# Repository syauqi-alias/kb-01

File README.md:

# Komputer Basikal, KB-01

**KB-01** is a high-performance, open-source bike computer built around the Raspberry Pi Compute Module 5. Designed to function like a rugged PDA for cycling, it features NVMe storage, precise GNSS tracking, a full sensor cluster for ML-based dead reckoning, and a robust power management system with 4.5–7 hours of estimated runtime.

## 📋 Specifications

| Feature | Component / Detail |
| :--- | :--- |
| **Core** | Raspberry Pi CM5 (4GB RAM, quad Cortex-A76) |
| **Storage** | 250GB NVMe M.2 2230 (PCIe) |
| **Display** | Waveshare 3.5" LCD (MIPI DSI) |
| **GNSS** | ST Teseo-LIV4F with Taoglas FXP611.07.0092C (Passive Antenna) |
| **IMU** | Bosch BMI270 (Accel/Gyro, SPI) |
| **Magnetometer** | ST LIS2MDL (I2C) |
| **Barometer** | Bosch BMP390 (I2C) |
| **Temp/Humidity** | Sensirion SHT40 (I2C) |
| **Wheel Speed** | TI DRV5023FA (Continuous unipolar Hall switch, 30kHz BW) |
| **Battery** | 10,000mAh Li-ion 1160100 (3.7V / 37Wh) |
| **Charger** | TI BQ25895 (I2C-configurable, USB BC1.2 detection) |
| **Fuel Gauge** | Maxim MAX17048 (I2C) |
| **Boost Converter** | TI TPS61022 (5V output, 8A valley current limit) |
| **USB Mux** | TI TS3USB30E (2:1 USB 2.0, auto-switching via BQ25895 DSEL) |
| **User Input** | Rotary encoder (A/B + push) + 2 buttons |
| **Audio** | Passive electromagnetic buzzer (PWM-driven via 2N7002 N-FET) |
| **Connectivity** | USB 2.0 (device/peripheral mode for GPX file transfer + charging) |

## ⚡ Power System

The power architecture handles high current loads from the CM5 and NVMe while ensuring safe battery management.

```
USB-C → BQ25895 (VBUS) → SYS → TPS61022 (VIN) → 5V → CM5
                ↕
            Battery
```

* **Charger / Power Path:** [TI BQ25895](https://www.ti.com/product/BQ25895)
    * Charges the battery while simultaneously powering the system via SYS rail.
    * Integrated USB BC1.2 detection for automatic source identification (SDP/CDP/DCP).
    * Input Current Optimizer (ICO) negotiates maximum power from USB source.
    * Ship mode via BATFET for zero-quiescent shutdown.
* **Fuel Gauge:** [Maxim MAX17048](https://www.analog.com/en/products/max17048.html)
    * ModelGauge algorithm — no sense resistor required.
    * Provides accurate SoC% and voltage reporting over I2C.
* **Boost Converter:** [TI TPS61022](https://www.ti.com/product/TPS61022)
    * Provides a fixed 5V output from 3.0–4.5V battery input.
    * EN tied to VIN (always on when SYS is live); MODE tied to GND (PFM for light-load efficiency).
    * Feedback resistors: R1 = 732kΩ, R2 = 100kΩ (per TI reference design).
* **USB-C:**
    * CC1/CC2: 5.1kΩ pull-downs to GND (sink device).
    * D+/D−: Routed via TS3USB30E multiplexer — Channel 1 to BQ25895 (BC1.2 detection), Channel 2 to CM5 USB (data transfer).
    * Mux control: BQ25895 DSEL pin drives TS3USB30E SEL (automatic, no GPIO needed).
    * CM5 USB configured as device/peripheral via `dtoverlay=dwc2,dr_mode=peripheral`.
* **Battery Life:** ~4.5 hours (max load) to ~7 hours (typical load).

## 🔌 Bus Architecture

| Bus | GPIOs | Devices | Notes |
| :--- | :--- | :--- | :--- |
| **I2C1** | GPIO2/3 | BQ25895, MAX17048 | 1.8kΩ built-in pull-ups (do NOT add external) |
| **I2C2** | GPIO4/5 | LIS2MDL, BMP390, SHT40 | 4.7kΩ external pull-ups required |
| **SPI0** | GPIO8–11 | BMI270 | Mode 0, max 10MHz |
| **UART0** | GPIO14/15 | Teseo-LIV4F | 9600 baud default, TX/RX crossover |
| **DSI0** | DISP0 connector | Waveshare 3.5" | Copied from CM5 IO board |
| **PCIe** | PCIe connector | NVMe SSD | Copied from CM5 IO board |

## 📡 Sensor Cluster & ML Dead Reckoning

The sensor cluster enables ML-based location prediction when GNSS is unavailable (tunnels, dense tree cover, urban canyons).

* **Inputs:** BMI270 (acceleration/rotation), LIS2MDL (heading), BMP390 (altitude), DRV5023FA (wheel speed/distance)
* **Ground truth:** Teseo-LIV4F GNSS position during training
* **Approach:** Extended Kalman filter or RNN; wheel speed removes velocity drift ambiguity
* **Wheel Speed Sensor:** DRV5023FA is a continuous-sensing unipolar Hall switch (not sampled) with 30kHz bandwidth — it never misses a pulse regardless of wheel speed. Single south-facing magnet on spoke, open-drain output with 10kΩ pull-up.

## 🔊 Audio Alerts

A passive electromagnetic buzzer (e.g. MLT-8530) driven by PWM on GPIO7 through a 2N7002 N-channel MOSFET. Used for turn-by-turn navigation alerts, speed warnings, button feedback, and low battery warnings.

```
GPIO7 → 100Ω → gate ──┬── 2N7002 drain ──── Buzzer (−)
                       │                          │
                     10kΩ                     Buzzer (+) → 3.3V
                       │                          │
                      GND              1N4148 ──|◄──┘ (flyback diode)
```

## 🖥️ Software Architecture

* **Language:** C (with pthreads for multi-core)
* **GUI:** LVGL (renders directly to framebuffer, no X11/Wayland)
* **Kernel:** PREEMPT_RT patched Linux for deterministic interrupt handling
* **Core allocation:**
    * Core 0 — UI rendering + wheel speed ISR (highest priority)
    * Core 1 — Sensor acquisition (I2C/SPI reads)
    * Core 2 — GNSS processing (UART/NMEA parsing)
    * Core 3 — ML inference + data logging

## 🛠️ Hardware Design Notes

* **Space Optimization:** The boost converter is placed underneath the M.2 NVMe drive clearance to minimize the PCB footprint.
* **Antenna:** Uses a passive flexible polymer antenna (Taoglas FXP611) for GNSS.
* **Mounting:** Designed to accommodate standard 3.5" display mounting points.
* **GPIO0:** Left as spare — HAT EEPROM pin (I2C0/ID_SD), available for future expansion.

### Layer Stackup (6-layer, 1.6 mm, AISLER)

Stackup source: [AISLER 6-layer 1.6 mm 35 µm](https://community.aisler.net/t/6-layers-1-6mm-35-m-stackup/5458). Copper is 35 µm on all layers. Impedance-controlled nets stay on the outer layers only, referenced to the adjacent solid GND plane (same approach as the Raspberry Pi CM5 IO board).

```
Layer    Role                     Reference   Dielectric below
F.Cu     Signal — low-speed       In1 GND     2 × 2116 prepreg, 230 µm, Er 4.25
In1.Cu   GND plane — never split  —           FR4 core,          300 µm, Er 4.5
In2.Cu   Signal — GPIO / SD / I2C In1 GND     3 × 2116 prepreg, 345 µm, Er 4.25
In3.Cu   Power — split pours      —           FR4 core,          300 µm, Er 4.5
In4.Cu   GND plane — never split  —           2 × 2116 prepreg, 230 µm, Er 4.25
B.Cu     Signal — high-speed      In4 GND     —
```

* **B.Cu (high-speed side):** CM5 module, M.2 NVMe, DSI connector, Teseo GNSS and SMA are all on B.Cu, so PCIe, DSI0 and the GNSS RF trace route bottom-to-bottom with no layer changes. Net classes: `DP_90_Outer` (PCIe, USB 2.0), `DP_100_Outer` (DSI0), `SE_50_Outer` (GNSS RF).
* **F.Cu:** USB-C, charger, fuel gauge, sensors, UI. USB 2.0 D+/D− (J3 → TS3USB30E → BQ25895) stays on F.Cu.
* **In2.Cu:** route predominantly one axis (along the 120 mm dimension) — it faces In3 with no plane between them.
* **In3.Cu:** pours only, no traces: `+5V`, `Vsys`, `+3V3`, `VBUS`, `+1.8v`, `3.3V_GNSS`, `M.2_3v3`.
* **Stitching:** via fence between In1 and In4 along the RF trace and around the CM5 high-speed region. Fill unused In2 area with GND to balance copper against In3.

See [ROUTING.md](ROUTING.md) for the routing order and per-net constraints.

## ⚙️ config.txt

```ini
dtparam=i2c_arm=on
dtoverlay=i2c2-pi5,pins_4_5
dtparam=spi=on
enable_uart=1
dtoverlay=dwc2,dr_mode=peripheral
```

## ⚠️ Disclaimer

This project is currently in the **prototype/brainstorming phase**.

* Battery life estimates (4.5–7 hours) are theoretical and based on datasheet typical values.
* USB-PD is not supported with passive CC resistors (5V input only).
* The CM5 + NVMe combination draws significant power — consider NVMe power states for optimisation.

## 🔗 References & Credits

* Designed by [Syauqi Alias](https://syauqi-alias.github.io/)
* Read the full project log here: [Projects Brainstorming](https://syauqi-alias.github.io/jekyll/2023-06-10-idea.html#komputer-basikal-kb-01-bike-computer)

## 📄 License

[MIT License](LICENSE)

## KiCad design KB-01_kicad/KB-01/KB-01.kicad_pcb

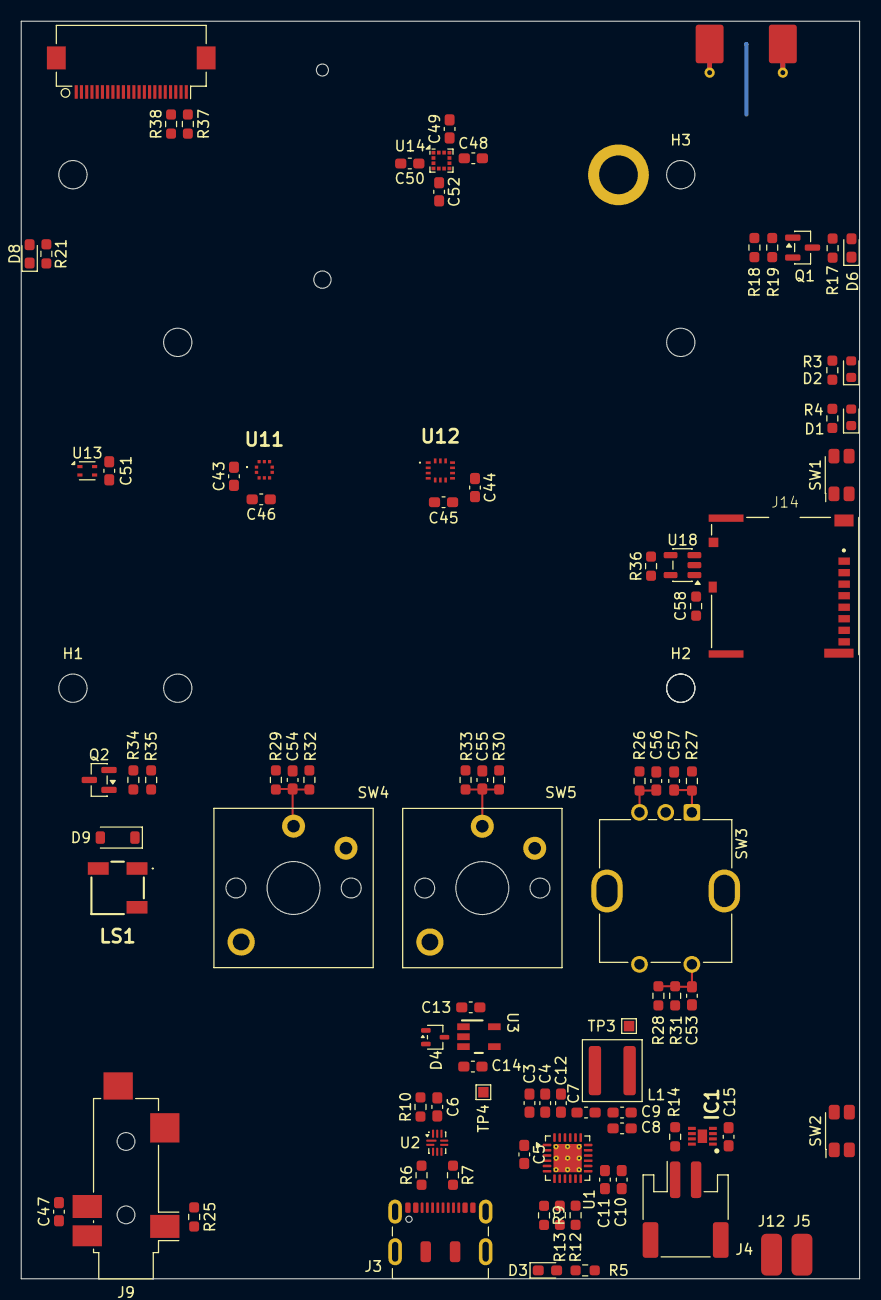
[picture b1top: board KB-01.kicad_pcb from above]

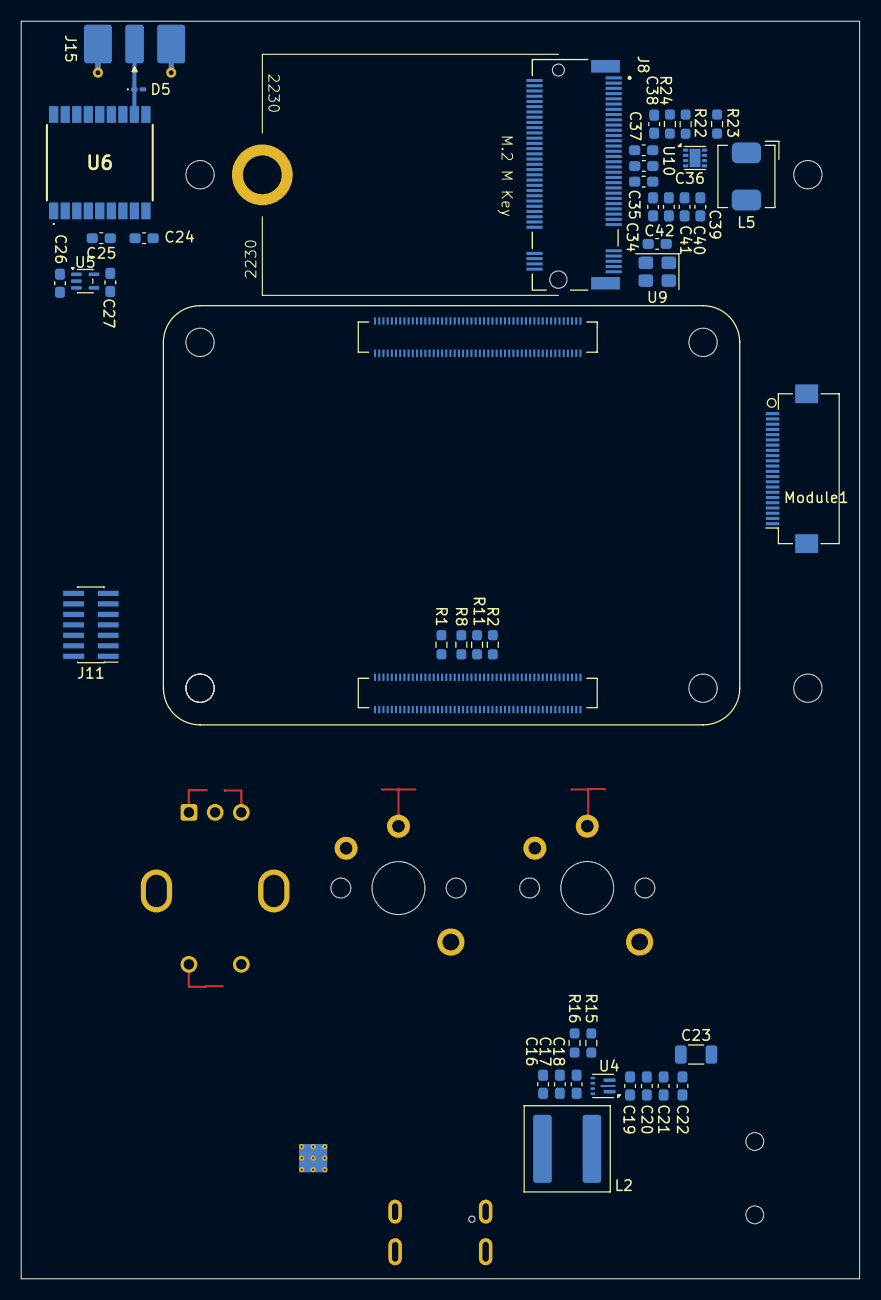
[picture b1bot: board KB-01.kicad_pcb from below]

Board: 6 copper layers, 80.0 x 120.0 mm, 138 parts (43 on the bottom side), 127 nets.

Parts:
C3, C8, C9, C10: 10uF 25V; C_0603_1608Metric_Pad1.08x0.95mm_HandSolder
C4, C11, C15: 0.1uF 25V; C_0603_1608Metric_Pad1.08x0.95mm_HandSolder
C5, C13: 1uF 25V; C_0603_1608Metric_Pad1.08x0.95mm_HandSolder
C6, C34, C37, C47: 0.1uF 10V; C_0603_1608Metric_Pad1.08x0.95mm_HandSolder
C7: 47nF 25V; C_0603_1608Metric_Pad1.08x0.95mm_HandSolder
C12, C14: 4.7uF 16V; C_0603_1608Metric_Pad1.08x0.95mm_HandSolder
C16, C17, C19, C20, C21, C22: 22uF 16V; C_0603_1608Metric_Pad1.08x0.95mm_HandSolder
C18: 0.1uF 16V; C_0603_1608Metric_Pad1.08x0.95mm_HandSolder
C23: 47uF 16V; R_1206_3216Metric
C24, C43, C44, C45, C46, C48, C50, C51, C53, C54, C55, C56, C57: 100nF 6.3V; C_0603_1608Metric_Pad1.08x0.95mm_HandSolder
C25, C49: 10uF 6.3V; C_0603_1608Metric_Pad1.08x0.95mm_HandSolder
C26, C27: 1uF 16V; C_0603_1608Metric_Pad1.08x0.95mm_HandSolder
C35, C36, C39, C40, C41, C42: 10uF10V; C_0603_1608Metric_Pad1.08x0.95mm_HandSolder
C38: 4.7nF 10V; C_0603_1608Metric_Pad1.08x0.95mm_HandSolder
C52: 220nF 25V; C_0603_1608Metric_Pad1.08x0.95mm_HandSolder
C58: 10uF 6.3V; R_0603_1608Metric_Pad0.98x0.95mm_HandSolder
D1: LED Green; LED_0603_1608Metric
D2: LED Red; LED_0603_1608Metric
D3, D8: Green; D_0603_1608Metric_Pad1.05x0.95mm_HandSolder
D4: BAT54-05W; SOT-323_SC-70
D5: SM15T36CA; D_0201_0603Metric_Pad0.64x0.40mm_HandSolder
D6: LED Red; LED_0603_1608Metric_Pad1.05x0.95mm_HandSolder
D9: 1N4148W; D_SOD-123
H1, H2, H3, H4: MountingHole; MountingHole_2.7mm_M2.5_DIN965
IC1: MAX17048G+T10; SON50P200X200X80-9N-D
J1, J13: Conn_01x22_MountingPin; Hirose_FH12-22S-0.5SH_1x22-1MP_P0.50mm_Horizontal
J3: USB_C_Receptacle_USB2.0_14P; USB_C_Receptacle_JAE_DX07S016JA1R1500
J4: Conn_01x02_MountingPin; JST_PH_S2B-PH-SM4-TB_1x02-1MP_P2.00mm_Horizontal
J5, J12: Conn_01x01_Socket; SolderWirePad_1x01_SMD_2x4mm
J8: Bus_M.2_Socket_M; M.2 M Key socket
J9: AudioJack3_SwitchTR; Jack_3.5mm_CUI_SJ2-3593D-SMT_Horizontal
J11: Conn_02x07_Odd_Even; PinHeader_2x07_P1.00mm_Vertical_SMD
J14: Micro_SD_Card_Det; SDCARD_MOLEX_503398-1892
J15: Conn_Coaxial; SMA_Molex_73251-2120_EdgeMount_Horizontal
L1: 1.0uH; L_Coilcraft_XAL5030-XXX
L2: 1uH 21.8A; L_Coilcraft_XAL7030-102
L5: 2.2uH; L_Bourns_SRP5030CC
LS1: CMT-0502-03-SMT-TR; CMT050203SMTTR
Module1: ComputeModule5-CM5; Raspberry-Pi-5-Compute-Module
Q1: MMBT3904; SOT-23
Q2: 2N7002; SOT-23
R1, R2, R18: 4.7k; R_0603_1608Metric_Pad0.98x0.95mm_HandSolder
R3, R4, R21, R31, R32, R33: 1k; R_0603_1608Metric_Pad0.98x0.95mm_HandSolder
R5: 2.21K; R_0603_1608Metric_Pad0.98x0.95mm_HandSolder
R6, R7: 5.1k; R_0603_1608Metric_Pad0.98x0.95mm_HandSolder
R8, R10, R11, R12, R13, R14, R19, R25, R26, R27, R28, R29, R30, R35: 10k; R_0603_1608Metric_Pad0.98x0.95mm_HandSolder
R9: 133; R_0603_1608Metric_Pad0.98x0.95mm_HandSolder
R15: 750k; R_0603_1608Metric_Pad0.98x0.95mm_HandSolder
R16: 100k; R_0603_1608Metric_Pad0.98x0.95mm_HandSolder
R17: 330; R_0603_1608Metric_Pad0.98x0.95mm_HandSolder
R22, R36: 10K 1%; R_0603_1608Metric_Pad0.98x0.95mm_HandSolder
R23: 100k 1%; R_0603_1608Metric_Pad0.98x0.95mm_HandSolder
R24, R37, R38: 2.2K 1%; R_0603_1608Metric_Pad0.98x0.95mm_HandSolder
R34: 180; R_0603_1608Metric_Pad0.98x0.95mm_HandSolder
SW1: Right angle Tact button; SW_SPST_EVQP7A
SW2: Power button; SW_SPST_EVQP7A
SW3: RotaryEncoder_Switch_MP; RotaryEncoder_Bourns_Vertical_PEC12R-3x17F-Sxxxx
SW4, SW5: SW_Push; SW_Kailh_Choc_V1V2_1.00u
TP3, TP4: TestPoint; TestPoint_Pad_1.0x1.0mm
U1: BQ25895; Texas_RTW_WQFN-24-1EP_4x4mm_P0.5mm_EP2.7x2.7mm_ThermalVias
U2: TS3USB30ERSWR; UQFN-10_1.4x1.8mm_P0.4mm
U3: TLV70430DBVR; DBV0005A_M
U4: TPS61022; Texas_RWU0007A_VQFN-7_2x2mm_P0.5mm
U5: TLV773_SOT353; SOT-353_SC-70-5
U6: TESEO-LIV4F; TESEOLIV4FTR
U9: ASEK-32.768KHZ-L-R-T; Crystal_SMD_3225-4Pin_3.2x2.5mm
U10: AP3441SHE-7B; DFN-8-1EP_2x2mm_P0.5mm_EP1.05x1.75mm
U11: BMP581
U12: BMI270
U13: SHT40; Sensirion_DFN-4_1.5x1.5mm_P0.8mm_SHT4x_NoCentralPad
U14: LIS2MDL; LGA-12_2x2mm_P0.5mm
U18: RT9742GGJ5 / NCP380HSN10AAT1G; SOT-23-5

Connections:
+3V3: C43.2, C44.1, C45.1, C46.1, C47.1, C48.1, C49.1, C50.1, C51.1, D1.2 (A), D2.2 (A), D9.1 (K), J1.22, J9.R, J9.RN, J13.22, LS1.1 (+), Module1.78 (GPIO_VREF(1.8v/3.3v_Input)), Module1.84 (+3.3v_(Output)), Module1.86 (+3.3v_(Output)), R1.1, R2.1, R25.1, R26.1, R27.1, R28.1, R29.1, R30.1, R36.1, R37.1, R38.1, U11.1 (VDDIO), U11.5 (SDO), U11.6 (CSB), U11.10 (VDD), U12.5 (VDDIO), U12.8 (VDD), U13.3 (VDD), U14.3 (~CS), U14.9 (Vdd), U14.10 (Vdd_IO), U18.5 (IN)
+3V_CHRG: C6.1, C14.1, Module1.76 (VBAT), R8.1, R10.2, R14.1, TP4.1 (1_1), U2.9 (VCC), U3.3 (OUT)
+5V: C19.1, C20.1, C21.1, C22.1, C23.1, C26.1, C35.1, C36.1, C37.1, Module1.77 (+5v_(Input)), Module1.79 (+5v_(Input)), Module1.81 (+5v_(Input)), Module1.83 (+5v_(Input)), Module1.85 (+5v_(Input)), Module1.87 (+5v_(Input)), R15.1, U4.3 (VOUT), U5.1 (IN), U10.3 (VIN)
/Battery_charger/CHG_D+: U1.2 (D+), U2.1 (D1+)
/Battery_charger/CHG_D-: U1.3 (D-), U2.7 (D1-)
/Battery_charger/Fuel_G: C10.1, C11.1, C15.1, D4.2 (A), IC1.2 (CELL), IC1.3 (VDD), J4.1, U1.13 (BAT), U1.14 (BAT)
/Battery_charger/MUX_D+: Module1.105 (USB2_P), U2.2 (D2+)
/Battery_charger/MUX_D-: Module1.103 (USB2_N), U2.6 (D2-)
/Battery_charger/RESET: SW2.2, U1.12 (~QON)
/Battery_charger/SEL: R10.1, U1.24 (DSEL), U2.10 (S)
/Battery_charger/USB_D+: J3.A6 (D+), J3.B6 (D+), U2.5 (D-)
/Battery_charger/USB_D-: J3.A7 (D-), J3.B7 (D-), U2.3 (D+)
/Battery_charger/Vsys: C8.1, C9.1, C16.1, C17.1, C18.1, L1.2, L2.1, R5.2, TP3.1 (1_1), U1.15 (SYS), U1.16 (SYS), U4.5 (EN), U4.7 (VIN)
/CM5_GPIO/+1.8v: Module1.88 (+1.8v_(Output)), Module1.90 (+1.8v_(Output))
/CM5_GPIO/CAM_GPIO0: J13.17, Module1.97 (CAM_GPIO0)
/CM5_GPIO/CAM_GPIO1: J9.S, Module1.100 (CAM_GPIO1), R25.2
/CM5_GPIO/EEPROM_nWP: J11.4, Module1.20 (EEPROM_nWP)
/CM5_GPIO/GPIO2: IC1.8 (SDA), Module1.58 (GPIO2), U1.6 (SDA)
/CM5_GPIO/GPIO3: IC1.7 (SCL), Module1.56 (GPIO3), U1.5 (SCL)
/CM5_GPIO/GPIO4: Module1.54 (GPIO4), R2.2, U11.4 (SDI), U13.1 (SDA), U14.4 (SDA/SDI/SDO)
/CM5_GPIO/GPIO5: Module1.34 (GPIO5), R1.2, U11.2 (SCK), U13.2 (SCL), U14.1 (SCL/SPC)
/CM5_GPIO/GPIO6: Module1.30 (GPIO6), R33.1
/CM5_GPIO/GPIO7: Module1.37 (GPIO7), R34.1
/CM5_GPIO/GPIO8: Module1.39 (GPIO8), U12.12 (CSB)
/CM5_GPIO/GPIO9: Module1.40 (GPIO9), U12.1 (SDO)
/CM5_GPIO/GPIO10: Module1.44 (GPIO10), U12.14 (SDX)
/CM5_GPIO/GPIO11: Module1.38 (GPIO11), U12.13 (SCX)
/CM5_GPIO/GPIO12: C57.1, Module1.31 (GPIO12), R27.2, SW3.A
/CM5_GPIO/GPIO13: C56.1, Module1.28 (GPIO13), R26.2, SW3.B
/CM5_GPIO/GPIO14: Module1.55 (GPIO14), U6.3 (UART-RX)
/CM5_GPIO/GPIO15: Module1.51 (GPIO15), U6.2 (UART-TX)
/CM5_GPIO/GPIO16: Module1.29 (GPIO16), U6.9 (~RESET)
/CM5_GPIO/GPIO17: Module1.50 (GPIO17), R11.1, U1.9 (~CE)
/CM5_GPIO/GPIO18: Module1.49 (GPIO18), R31.2
/CM5_GPIO/GPIO19: Module1.26 (GPIO19), R32.1
/CM5_GPIO/GPIO20: Module1.27 (GPIO20), U6.5 (WAKEUP)
/CM5_GPIO/GPIO21: Module1.25 (GPIO21), U5.3 (EN)
/CM5_GPIO/GPIO22: IC1.5 (~ALRT), Module1.46 (GPIO22), R14.2
/CM5_GPIO/GPIO23: Module1.47 (GPIO23), U12.4 (INT1)
/CM5_GPIO/GPIO24: Module1.45 (GPIO24), U14.7 (DRDY)
/CM5_GPIO/GPIO25: Module1.41 (GPIO25), U11.7 (INT)
/CM5_GPIO/GPIO26: Module1.24 (GPIO26), U12.9 (INT2)
/CM5_GPIO/GPIO27: Module1.48 (GPIO27), R8.2, U1.7 (~INT)
/CM5_GPIO/ID_SC: J13.20, Module1.35 (ID_SC), R38.2
/CM5_GPIO/ID_SD: J13.21, Module1.36 (ID_SD), R37.2
/CM5_GPIO/PMIC_ENABLE: J11.12, Module1.99 (PMIC_ENABLE)
/CM5_GPIO/PWR_BUT: J11.14, Module1.92 (PWR_BUT), SW1.1
/CM5_GPIO/SD_CLK: J14.5 (CLK), Module1.57 (SD_CLK)
/CM5_GPIO/SD_CMD: J14.3 (CMD), Module1.62 (SD_CMD)
/CM5_GPIO/SD_DAT0: J14.7 (DAT0), Module1.63 (SD_DAT0)
/CM5_GPIO/SD_DAT1: J14.8 (DAT1), Module1.67 (SD_DAT1)
/CM5_GPIO/SD_DAT2: J14.1 (DAT2), Module1.69 (SD_DAT2)
/CM5_GPIO/SD_DAT3: J14.2 (DAT3/CD), Module1.61 (SD_DAT3)
/CM5_GPIO/SD_PWR: C58.1, J14.4 (VDD), U18.1 (OUT)
/CM5_GPIO/SD_PWR_ON: Module1.75 (SD_PWR_ON), R36.2, U18.4 (EN)
/CM5_GPIO/SYNC_OUT: J11.6, Module1.18 (Ethernet_SYNC_OUT(3.3v))
/CM5_GPIO/USBOTG: J11.10, Module1.101 (USB_OTG_ID)
/CM5_GPIO/nPWR_LED: Module1.95 (LED_nPWR), R3.2
/CM5_GPIO/nRPIBOOT: J11.2, Module1.93 (nRPIBOOT)
/CM5_high_speed/DPHY0_C_N: J1.8, Module1.127 (MIPI0_C_N)
/CM5_high_speed/DPHY0_C_P: J1.9, Module1.129 (MIPI0_C_P)
/CM5_high_speed/DPHY0_D0_N: J1.2, Module1.115 (MIPI0_D0_N)
/CM5_high_speed/DPHY0_D0_P: J1.3, Module1.117 (MIPI0_D0_P)
/CM5_high_speed/DPHY0_D1_N: J1.5, Module1.121 (MIPI0_D1_N)
/CM5_high_speed/DPHY0_D1_P: J1.6, Module1.123 (MIPI0_D1_P)
/CM5_high_speed/DPHY0_D2_N: J1.11, Module1.133 (MIPI0_D2_N)
/CM5_high_speed/DPHY0_D2_P: J1.12, Module1.135 (MIPI0_D2_P)
/CM5_high_speed/DPHY0_D3_N: J1.14, Module1.139 (MIPI0_D3_N)
/CM5_high_speed/DPHY0_D3_P: J1.15, Module1.141 (MIPI0_D3_P)
/CM5_high_speed/DPHY1_C_N: J13.8, Module1.187 (MIPI1_C_N)
/CM5_high_speed/DPHY1_C_P: J13.9, Module1.189 (MIPI1_C_P)
/CM5_high_speed/DPHY1_D0_N: J13.2, Module1.175 (MIPI1_D0_N)
/CM5_high_speed/DPHY1_D0_P: J13.3, Module1.177 (MIPI1_D0_P)
/CM5_high_speed/DPHY1_D1_N: J13.5, Module1.181 (MIPI1_D1_N)
/CM5_high_speed/DPHY1_D1_P: J13.6, Module1.183 (MIPI1_D1_P)
/CM5_high_speed/DPHY1_D2_N: J13.11, Module1.193 (MIPI1_D2_N)
/CM5_high_speed/DPHY1_D2_P: J13.12, Module1.195 (MIPI1_D2_P)
/CM5_high_speed/DPHY1_D3_N: J13.14, Module1.194 (MIPI1_D3_N)
/CM5_high_speed/DPHY1_D3_P: J13.15, Module1.196 (MIPI1_D3_P)
/CM5_high_speed/PCIE_CLK_N: J8.53 (REFCLKn), Module1.112 (PCIe_CLK_N)
/CM5_high_speed/PCIE_CLK_P: J8.55 (REFCLKp), Module1.110 (PCIe_CLK_P)
/CM5_high_speed/PCIE_PWR_EN: Module1.106 (PCIE_PWR_EN), R23.1, U10.7 (EN)
/CM5_high_speed/PCIE_RX_N: J8.43 (PETp0), Module1.118 (PCIe_RX_N)
/CM5_high_speed/PCIE_RX_P: J8.41 (PETn0), Module1.116 (PCIe_RX_P)
/CM5_high_speed/PCIE_TX_N: J8.49 (PERp0), Module1.124 (PCIe_TX_N)
/CM5_high_speed/PCIE_TX_P: J8.47 (PERn0), Module1.122 (PCIe_TX_P)
/CM5_high_speed/PCIE_nCLKREQ: J8.52 (~CLKREQ), Module1.102 (PCIe_nCLKREQ)
/CM5_high_speed/PCIE_nRST: J8.50 (~PERST), Module1.109 (PCIe_nRST)
/CM5_high_speed/PCIE_nWAKE: J8.54 (~PEWAKE), Module1.104 (PCIE_nWAKE)
/CM5_high_speed/SCL0: J1.20, Module1.80 (SCL0)
/CM5_high_speed/SDA0: J1.21, Module1.82 (SDA0)
/GNSS/3.3V_GNSS: C24.1, C25.1, C27.1, R17.1, U5.5 (OUT), U6.6 (VBAT), U6.8 (VCC)
/GNSS/GNSS_PPS: R18.1, U6.4 (PPS)
/PCIe_NVMe/FB: C38.2, R22.2, R24.1, U10.1 (FB)
/PCIe_NVMe/M.2_3v3: C34.1, C38.1, C39.1, C40.1, C41.1, C42.1, D8.2 (A), J8.2 (3.3V), J8.4 (3.3V), J8.12 (3.3V), J8.14 (3.3V), J8.16 (3.3V), J8.18 (3.3V), J8.70 (3.3V), J8.72 (3.3V), J8.74 (3.3V), L5.2, R22.1, U9.1 (EN), U9.4 (VDD)
GND: C3.2, C4.2, C5.2, C6.2, C8.2, C9.2, C10.2, C11.2, C12.2, C13.2, C14.2, C15.2, C16.2, C17.2, C18.2, C19.2, C20.2, C21.2, C22.2, C23.2, C24.2, C25.2, C26.2, C27.2, C34.2, C35.2, C36.2, C37.2, C39.2, C40.2, C41.2, C42.2, C43.1, C44.2, C45.2, C46.2, C47.2, C48.2, C49.2, C50.2, C51.2, C52.2, C53.2, C54.2, C55.2, C56.2, C57.2, C58.2, D5.2 (A2), IC1.1 (CTG), IC1.4 (GND), IC1.6 (QSTRT), IC1.9 (EP), J1.1, J1.4, J1.7, J1.10, J1.13, J1.16, J1.19, J1.MP (MountPin), J3.A1 (GND), J3.A12 (GND), J3.B1 (GND), J3.B12 (GND), J3.S1 (SHIELD), J4.2, J4.MP (MountPin), J8.1 (GND), J8.3 (GND), J8.9 (GND), J8.15 (GND), J8.21 (GND), J8.27 (GND), J8.33 (GND), J8.39 (GND), J8.45 (GND), J8.51 (GND), J8.57 (GND), J8.71 (GND), J8.73 (GND), J8.75 (GND), J8.M1 (GND2230), J8.S1, J8.S2, J9.T, J9.TN, J11.1, J11.3, J11.5, J11.7, J11.9, J11.11, J11.13, J12.1 (Pin_1_1), J13.1, J13.4, J13.7, J13.10, J13.13, J13.16, J13.19, J13.MP (MountPin), J14.6 (VSS), J14.11 (SHIELD), J15.2 (Ext), Module1.1 (GND), Module1.2 (GND), Module1.7 (GND), Module1.8 (GND), Module1.13 (GND), Module1.14 (GND), Module1.22 (GND), Module1.23 (GND), Module1.32 (GND), Module1.33 (GND), Module1.42 (GND), Module1.43 (GND), Module1.52 (GND), Module1.53 (GND), Module1.59 (GND), Module1.60 (GND), Module1.65 (GND), Module1.66 (GND), Module1.71 (GND), Module1.74 (GND), Module1.98 (GND), Module1.107 (GND), Module1.108 (GND), Module1.113 (GND), Module1.114 (GND), Module1.119 (GND), Module1.120 (GND), Module1.125 (GND), Module1.126 (GND), Module1.131 (GND), Module1.132 (GND), Module1.137 (GND), Module1.138 (GND), Module1.144 (GND), Module1.150 (GND), Module1.155 (GND), Module1.156 (GND), Module1.161 (GND), Module1.162 (GND), Module1.167 (GND), Module1.168 (GND), Module1.173 (GND), Module1.174 (GND), Module1.179 (GND), Module1.180 (GND), Module1.185 (GND), Module1.186 (GND), Module1.191 (GND), Module1.192 (GND), Module1.197 (GND), Module1.198 (GND), Q1.2 (E), Q2.2 (S), R6.2, R7.1, R9.2, R11.2, R13.2, R16.2, R19.2, R23.2, R24.2, R35.1, SW1.2, SW2.1, SW3.C, SW3.MP, SW3.S2, SW4.2, SW5.2, U1.8 (OTG), U1.17 (PGND), U1.18 (PGND), U1.25 (PGND), U2.4 (GND), U2.8 (~OE), U3.1 (GND), U3.4 (NC), U3.5 (NC), U4.1 (GND), U4.6 (MODE), U5.2 (GND), U6.1 (GND), U6.10 (GND_RF), U6.12 (GND_RF), U9.2 (GND), U10.4 (PGND), U10.8 (SGND), U10.9 (PAD), U11.3 (VSS_1), U11.8 (VSS_2), U11.9 (VSS_3), U12.6 (GNDIO), U12.7 (GND), U13.4 (VSS), U14.6 (GND), U14.8 (GND), U18.2 (GND)
unnamed: C7.1, L1.1, U1.19 (SW), U1.20 (SW)
unnamed: C53.1, R28.2, R31.1, SW3.S1
unnamed: C54.1, R29.2, R32.2, SW4.1
unnamed: C55.1, R30.2, R33.2, SW5.1
unnamed: D1.1 (K), R4.1
unnamed: D2.1 (K), R3.1
unnamed: D3.2 (A), R5.1
unnamed: D3.1 (K), U1.4 (STAT)
unnamed: C13.1, D4.3 (K), U3.2 (IN)
unnamed: D5.1 (A1), J15.1 (In), U6.11 (RF_IN)
unnamed: D6.2 (A), R17.2
unnamed: D6.1 (K), Q1.3 (C)
unnamed: D8.1 (K), R21.1
unnamed: D9.2 (A), LS1.2 (-), Q2.3 (D)
unnamed: J3.A5 (CC1), R6.1
unnamed: J3.B5 (CC2), R7.2
unnamed: J5.1 (Pin_1_1), R12.2, R13.1, U1.11 (TS)
unnamed: J8.10 (DAS/~DSS/~LED1), R21.2
unnamed: J8.68 (SUSCLK), U9.3 (Out)
unnamed: Module1.21 (LED_nACT), R4.2
unnamed: Q1.1 (B), R18.2, R19.1
unnamed: Q2.1 (G), R34.2, R35.2
unnamed: C7.2, U1.21 (BTST)
unnamed: R9.1, U1.10 (ILIM)
unnamed: C3.1, C4.1, U1.23 (PMID)
unnamed: C12.1, R12.1, U1.22 (REGN)
unnamed: R15.2, R16.1, U4.4 (FB)
unnamed: L2.2, U4.2 (SW)
unnamed: L5.1, U10.6 (LX)
unnamed: C52.1, U14.5 (C1)
VBUS: C5.1, D4.1 (A), J3.A4 (VBUS), J3.A9 (VBUS), J3.B4 (VBUS), J3.B9 (VBUS), U1.1 (VBUS)

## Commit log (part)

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2025-12-23 push
2026-01-29 all v2
2026-02-04 update gnss
2026-02-12 everything
2026-02-22 Revise README with updated specs and power details
    Updated specifications and power system details for KB-01 bike computer. Enhanced description and added new features for sensors, battery, and architecture.
